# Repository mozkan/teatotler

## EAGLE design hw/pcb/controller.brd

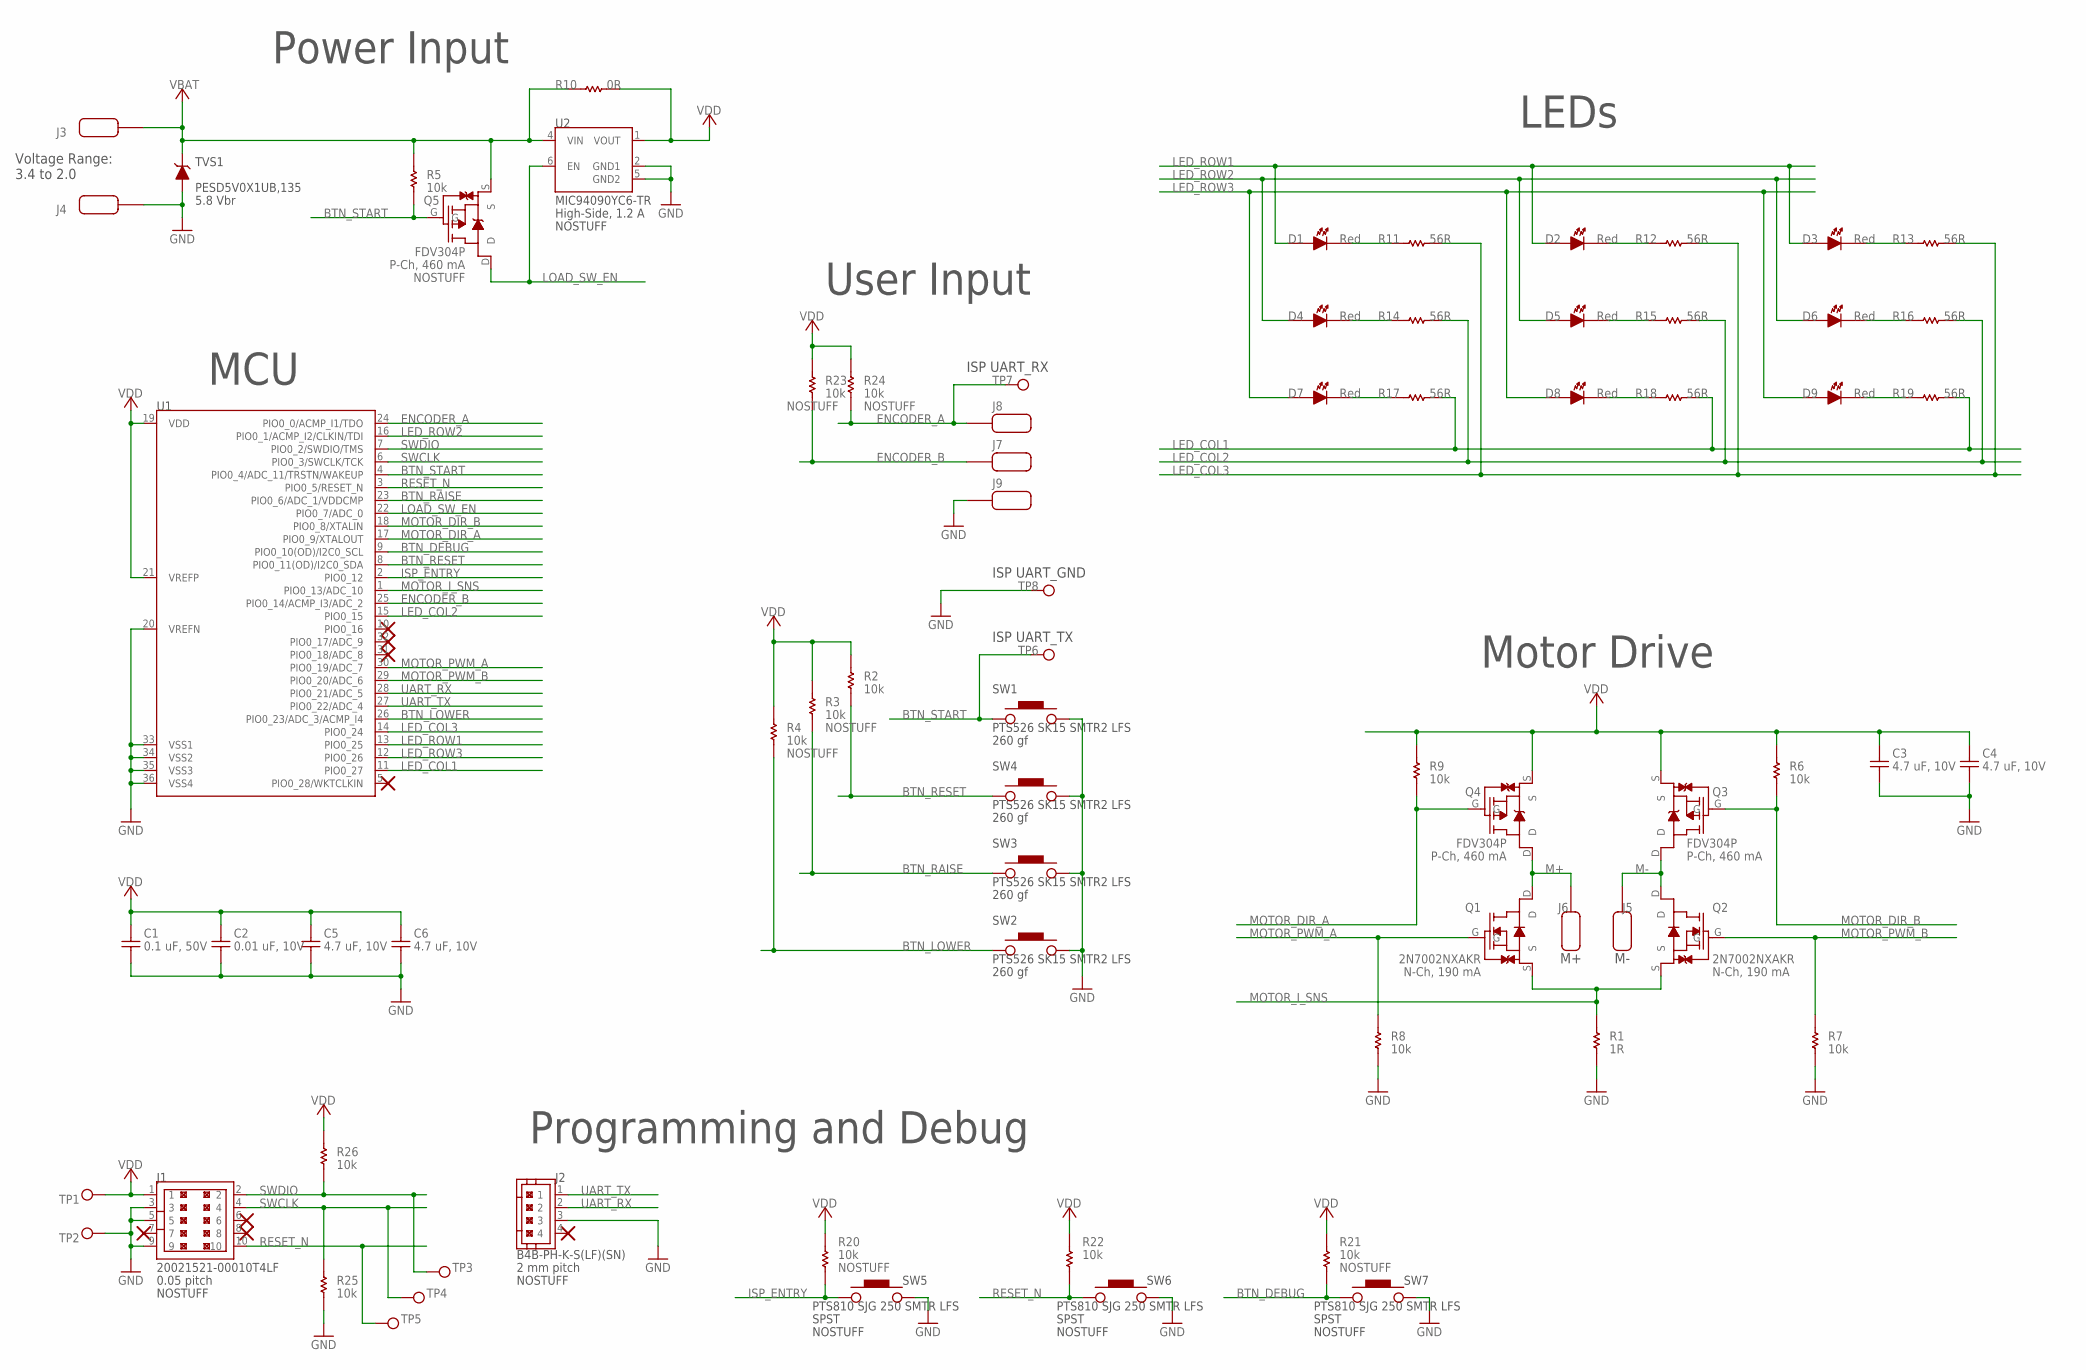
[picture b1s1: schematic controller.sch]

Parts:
C1: CAP_C1608X7R1H104K080AA; CAP_0603
C2: CAP_CL10B103KB8NNNC; CAP_0603
C3, C4, C5, C6: CAP_CGB3B1X5R1A475M055AC; CAP_0603
D1, D2, D3, D4, D5, D6, D7, D8, D9: LED_150060RS75000; LED_0603
J1: 20021521-00010T4LF; HEADER_2X5_50MIL_SHROUDED_KEYED
J2: B4B-PH-K-S; JST-PH_2MM_TH
J3, J4, J5, J6, J7, J8, J9: PAD_1P4X3P25MM; PAD_1P4MM_X_3P25MM
Q1, Q2: 2N7002NXAKR; SOT-23_FET_GENERIC
Q3, Q4, Q5: FDV304P; SOT-23_FET_GENERIC
R1: RES_1R_RMCF0603FT1R00; RES_0603
R2, R3, R4, R5, R6, R7, R8, R9, R20, R21, R22, R23, R24, R25, R26: RES_10K_RC0603FR-0710KL; RES_0603
R10: RES_0R_RC0603JR-070RL; RES_0603
R11, R12, R13, R14, R15, R16, R17, R18, R19: RES_56R_RC0603FR-0756RL; RES_0603
SW1, SW2, SW3, SW4: PTS526_SK15_SMTR2_LFS; PTS526-G_LEAD
SW5, SW6, SW7: PTS810_SJG_250_SMTR_LFS; PTS810
TP1, TP2, TP3, TP4, TP5, TP6, TP7, TP8: TP_1P6_MM_ROUND
TVS1: PESD5V0X1UB,135; SOD523
U1: LPC822M101JHI33ELPC82X_VQFN33_HAND_SOLDER; LPC82X_VQFN33_HAND_SOLDER
U2: MIC94090YC6; SC-70-6_GENERIC

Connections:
BTN_DEBUG: R21.P$1, SW7.P1, U1.9 (PIO0_10(OD)/I2C0_SCL)
BTN_LOWER: R4.P$1, SW2.1, U1.26 (PIO0_23/ADC_3/ACMP_I4)
BTN_RAISE: R3.P$1, SW3.1, U1.23 (PIO0_6/ADC_1/VDDCMP)
BTN_RESET: R2.P$1, SW4.1, U1.8 (PIO0_11(OD)/I2C0_SDA)
BTN_START: Q5.G, R5.P$1, SW1.1, TP6.P$1, U1.4 (PIO0_4/ADC_11/TRSTN/WAKEUP)
ENCODER_A: J8.1, R24.P$1, TP7.P$1, U1.24 (PIO0_0/ACMP_I1/TDO)
ENCODER_B: J7.1, R23.P$1, U1.25 (PIO0_14/ACMP_I3/ADC_2)
GND: C1.P$2, C2.P$2, C3.P$2, C4.P$2, C5.P$2, C6.P$2, J1.3, J1.5, J1.9, J2.3, J4.1, J9.1, R1.P$1, R7.P$1, R8.P$1, R25.P$1, SW1.3 (P2), SW2.3 (P2), SW3.3 (P2), SW4.3 (P2), SW5.P3 (P2), SW6.P3 (P2), SW7.P3 (P2), TP2.P$1, TP8.P$1, TVS1.A, U1.20 (VREFN), U1.33 (VSS1), U1.34 (VSS2), U1.35 (VSS3), U1.36 (VSS4), U2.2 (GND1), U2.5 (GND2)
ISP_ENTRY: R20.P$1, SW5.P1, U1.2 (PIO0_12)
LED_COL1: R17.P$2, R18.P$2, R19.P$2, U1.11 (PIO0_27)
LED_COL2: R14.P$2, R15.P$2, R16.P$2, U1.15 (PIO0_15)
LED_COL3: R11.P$2, R12.P$2, R13.P$2, U1.14 (PIO0_24)
LED_ROW1: D1.A, D2.A, D3.A, U1.13 (PIO0_25)
LED_ROW2: D4.A, D5.A, D6.A, U1.16 (PIO0_1/ACMP_I2/CLKIN/TDI)
LED_ROW3: D7.A, D8.A, D9.A, U1.12 (PIO0_26)
LOAD_SW_EN: Q5.D, U1.22 (PIO0_7/ADC_0), U2.6 (EN)
M+: J6.1, Q1.D, Q4.D
M-: J5.1, Q2.D, Q3.D
MOTOR_DIR_A: Q4.G, R9.P$1, U1.17 (PIO0_9/XTALOUT)
MOTOR_DIR_B: Q3.G, R6.P$1, U1.18 (PIO0_8/XTALIN)
MOTOR_I_SNS: Q1.S, Q2.S, R1.P$2, U1.1 (PIO0_13/ADC_10)
MOTOR_PWM_A: Q1.G, R8.P$2, U1.30 (PIO0_19/ADC_7)
MOTOR_PWM_B: Q2.G, R7.P$2, U1.29 (PIO0_20/ADC_6)
unnamed: D1.K, R11.P$1
unnamed: D4.K, R14.P$1
unnamed: D7.K, R17.P$1
unnamed: D2.K, R12.P$1
unnamed: D5.K, R15.P$1
unnamed: D8.K, R18.P$1
unnamed: D3.K, R13.P$1
unnamed: D6.K, R16.P$1
unnamed: D9.K, R19.P$1
RESET_N: J1.10, R22.P$1, SW6.P1, TP5.P$1, U1.3 (PIO0_5/RESET_N)
SWCLK: J1.4, R25.P$2, TP4.P$1, U1.6 (PIO0_3/SWCLK/TCK)
SWDIO: J1.2, R26.P$1, TP3.P$1, U1.7 (PIO0_2/SWDIO/TMS)
UART_RX: J2.2, U1.28 (PIO0_21/ADC_5)
UART_TX: J2.1, U1.27 (PIO0_22/ADC_4)
VBAT: J3.1, Q5.S, R5.P$2, R10.P$1, TVS1.K, U2.4 (VIN)
VDD: C1.P$1, C2.P$1, C3.P$1, C4.P$1, C5.P$1, C6.P$1, J1.1, Q3.S, Q4.S, R2.P$2, R3.P$2, R4.P$2, R6.P$2, R9.P$2, R10.P$2, R20.P$2, R21.P$2, R22.P$2, R23.P$2, R24.P$2, R26.P$2, TP1.P$1, U1.19 (VDD), U1.21 (VREFP), U2.1 (VOUT)

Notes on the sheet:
Power Input
LEDs
Programming and Debug
Motor Drive
User Input
Voltage Range: 3.4 to 2.0
MCU
ISP UART_TX
ISP UART_RX
ISP UART_GND

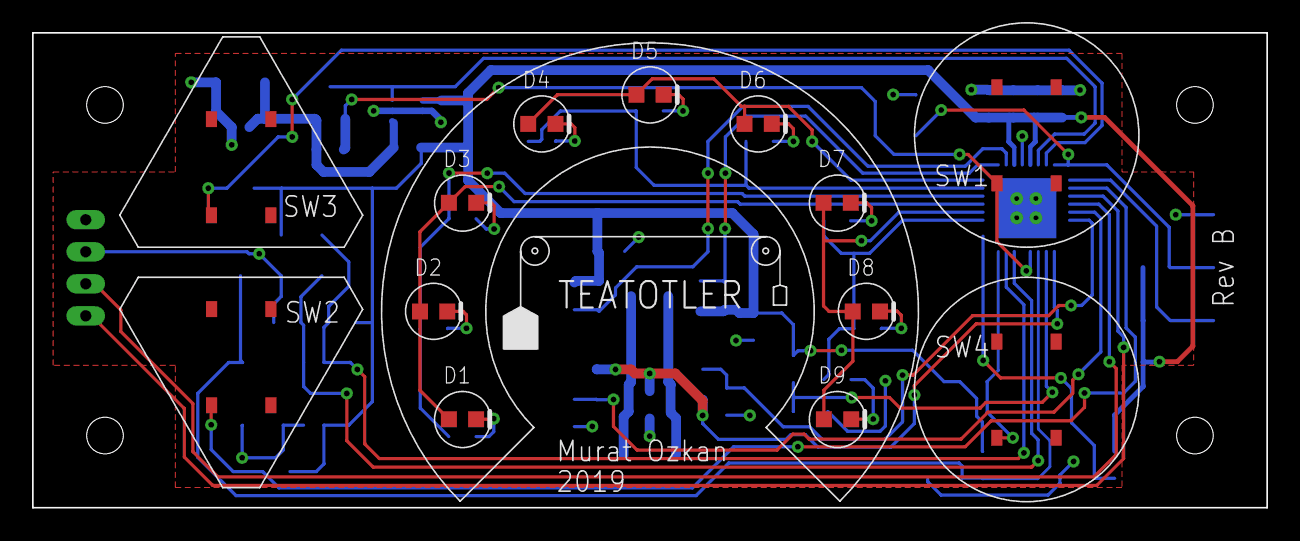
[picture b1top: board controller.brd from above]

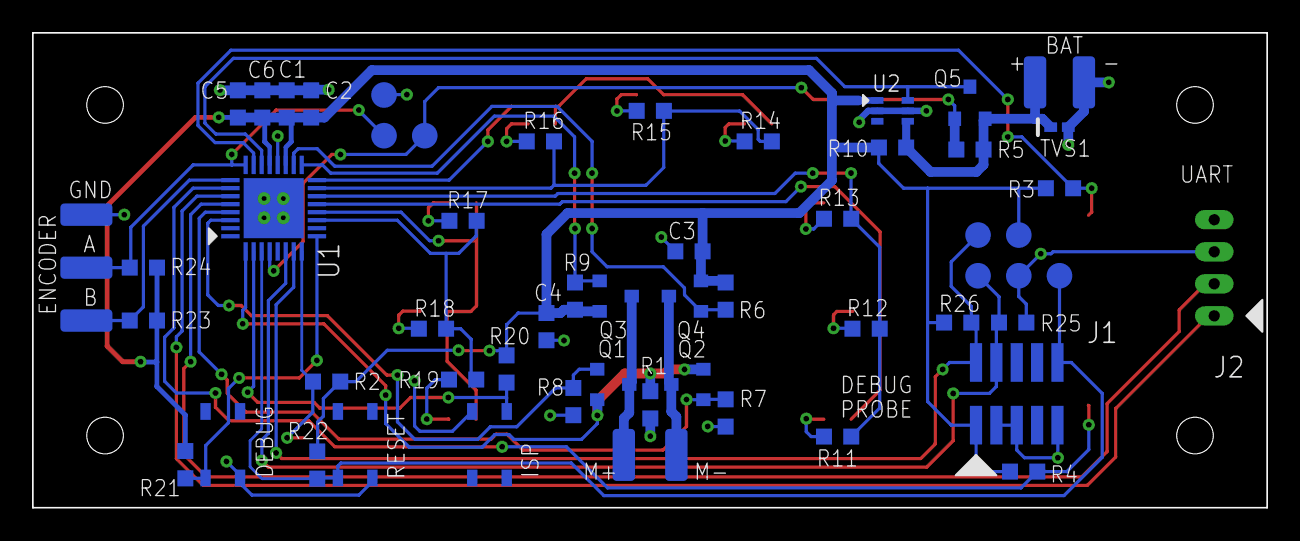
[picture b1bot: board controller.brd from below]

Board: 2 copper layers, 77.0 x 29.6 mm, 73 parts (60 on the bottom side), 39 nets.

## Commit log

2019-12-08 Initial commit of MCUXpresso project files
    This is the stock project for an MCUXpresso LPC822 C++ application.
    This compiles and can be loaded onto the LPC822 MCU on the Teatotler
    controller board. Further tweaks will follow to put this in a better
    place under the sw/ directory. An ide/ directory is additionally
    created to store these files.
2019-12-08 Updated directory structure
    Created an initial directory structure. Moved source directories for
    code not generated by the MCUXpresso IDE out of the ide/ directory.
    Created "Linked Resource" folders to map directories outside of the
    ide/ directory to the Eclipse project.
2019-12-08 Updated include paths
    Updated include paths to include the new linked directories.
2019-12-08 Initial set of peripheral sources
    Starting work on basic GPIO code for bringup.
2019-12-08 Basic GPIO input and MCU init done
    Got a basic GPIO input working. Configured all peripheral clocks that
    this application will eventually need.
2019-12-08 Tested user buttons
    User butons now work. Fixed small bug in GPIO class.
2019-12-08 Confirmed LEDs work
    Test code initializes LED array as I/O (instead of PWM). Works.
2019-12-08 Tested H-Bridge circuit
    Works in both directions.
2019-12-09 First commit of PCB design files
    These are the design files for Rev B of the PCB. We shall not speak
    of Rev A. RIP Rev A.
2019-12-12 Basic MRT driver works (no interrupts)
    This MRT driver uses a single channel (four available) and does not
    use interrupt-driven behavior. It must be polled to check whether the
    timer has timed reached zero.
2019-12-12 WIP - updating MCU class
2020-01-26 Updated I/O mappings for Rev B board
    Just did the first test of the Rev B board. Old bringup code still
    works. Motor is weak. Not sure why. Probably not software.
2020-01-26 Refactor MCU class and update compiler settings
    Refactored MCU class to produce IDigitalInput and IDigitalOutput
    objects derived from underlying GPIO types. Inheritance code adds
    about 1.5k of flash usage (15% of available flash). Heap allocation
    code adds another 1.5k of flash usage, and reserves about half of
    SRAM based on the way the linker script and initialization code is
    configured by default via MCUXpresso.
2020-01-26 Updated MCU class to produce IIntervalTimers
    Refactored MCU class to produce IIntervalTimer classes based on Mrt
    classes.
2020-04-02 Add display driver
    Add the display driver. Tested with reworked Rev B board to fix the
    mistake in the LED display. Added the ManagedDriver class to enable a
    consistent interface for driving such drivers from a singlethreaded
    environment with a simple wall clock timing reference.
    Updated compiler settings to remove disable exceptions that was
    growing the binary size considerably when using pure virtual
2020-04-02 Use newlib nano instead of newlib
    Oops. Didn't realize standard newlib was being used this whole time.
    Updated to use newlib-nano instead. Code now builds with
    --no-exceptions now as well, further reducing footprint.
2020-04-02 Add PeriodicTask class
    Add the PeriodicTask class to manage work done on a fixed time
    interval. This class should provide the interface through which all
    tasks in the system are run in the top-level control loop.
    This commit removes ManagedDriver, since PeriodicTasks turned out to
    be identical in its interface, and could apply equally to code in app/
    and system/. It lives in util/ for this reason.
2020-04-03 Add Teatotler class to manage system drivers
    - The Teatotler class now contains all system drivers.
    - Added PanelButtons class to manage all user facing button inputs.
    - Added DebouncedInput class to handle the debouncing of raw GPIO
    inputs so that PanelButtons just manages their sampling and
    retrieval of state.
2020-04-03 Updated H-Bridge driver with deadbanding
    Added a deadband function to the H-Bridge driver. It can now be thrown
    into forward from reverse and vice versa, and it will protect itself
    from momentary shoot-through by stopping first for a period of time.
2020-04-03 DebouncedInput class works as expected
    WIP commit. Test code checked in here.
2020-04-04 Integrate PanelButtons into Teatotler
    Tested PanelButtons in isolation, then again after integrating into
    the Teatotler class that now contains it.
2020-04-04 Add RotarySwitch encoder driver
    Added the RotarySwitch encoder driver. Test code currently translates
    rotations to paint up and down on the display like a tachometer.
    Also updated destructors on derived classes with virtual keyword
    (forgot first time around).
2020-04-04 Add skeleton Steeper class
    Moved prototyping code for testing Teatotler drivers in main() into
    the Steeper class where they belong. Re-tested some of the prototpying
    code from within Steeper to verify everything still works. Unit test
    environment would be nice...
2020-04-05 Add tick timer class and error handler
    Added a TickTimer class to encapsulate the timing functions performed
    manually in main() so far. This also contains an error handler set at
    runtime that shows a conspicuous (impossible under normal operating
    conditions) pattern on the indicator LEDs for 5 seconds.
    Moved ownership of Mcu class out of Teatotler. The Mcu, Teatotler, and
    Steeper instances all get created separately in main now.
2020-04-05 Partitioned state machine into state classes
    Since Steeper was getting fairly large, with a lot of data members, it
    is now composed of separate worker classes that each implement the
    state logic. The current functionality for the kSetSteepTime state has
    been ported to the first such state class SetSteepTime.
2020-04-05 Add SetDunkCount state
    Added the state class for the kSetDunkCount state, SetDunkCount.
2020-04-05 Add Steep state
    Added the state class for the kSteep state, Steep.
2020-04-19 Add Steep Complete state
    Added the final Steep Complete state that blinks the LEDs for 30
    seconds before (eventually) entering the sleep state (not implemented
    yet). Moved the lower and raise of the teabag out of the steep state
    so that it will only need to deal with dunking.
2020-04-19 Explicitly build using C++14 dialect
    Not sure what the default dialect is for GCC 8.3. I had assumed it was
    C++14 but this makes it explicit.
2020-04-19 Fix bug in steep time countdown
    Fix off by one error in counts to millisecond conversion logic.
2020-04-19 Add dunk logic
    Added the logic to handle dunking the teabag at the number dunks set
    in the dunk count parameter in the shared steep parameters. Dunks are
    evently spaced throughout the steeping duration.
2020-04-19 Update dunk count display to show whole numbers
    The dunk count display in the SteepState::kSetDunkCount state now
    shows only the pixels corresponding to the whole numbers on the
    indicator panel. This is a bit more intuitive and also caps the dunk
    count to something reasonable (5 dunks).
